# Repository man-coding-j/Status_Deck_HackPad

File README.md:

# Status_Deck_HackPad
Status_Deck is a fully custom-designed macro pad developed using the Seeed XIAO RP2040 microcontroller. The device incorporates a 2×3 diode-isolated key matrix, dual rotary encoders, and an I²C OLED display to provide real-time user feedback. The buttons are programmable to your needs, and this project was made for easy day-to-day use.

# Status_Deck

#Bill of Materials (BOM)

#| Item | Quantity | Description |

#| Seeed XIAO RP2040 | 1 | Microcontroller |

#| MX-style switches | 6 | Mechanical key switches |

#| 1N4148 Diodes | 6 | Matrix isolation |

#| Rotary Encoder | 2 | With push-button functionality |

#| 0.96" I²C OLED | 1 | SSD1306 display |

#| Keycaps | 6 | Compatible with MX switches |

#| Custom PCB | 1 | Designed in KiCad |

#| 3D Printed Case | 1 | Custom enclosure |

#| Screws / Standoffs | As needed | PCB mounting hardware |

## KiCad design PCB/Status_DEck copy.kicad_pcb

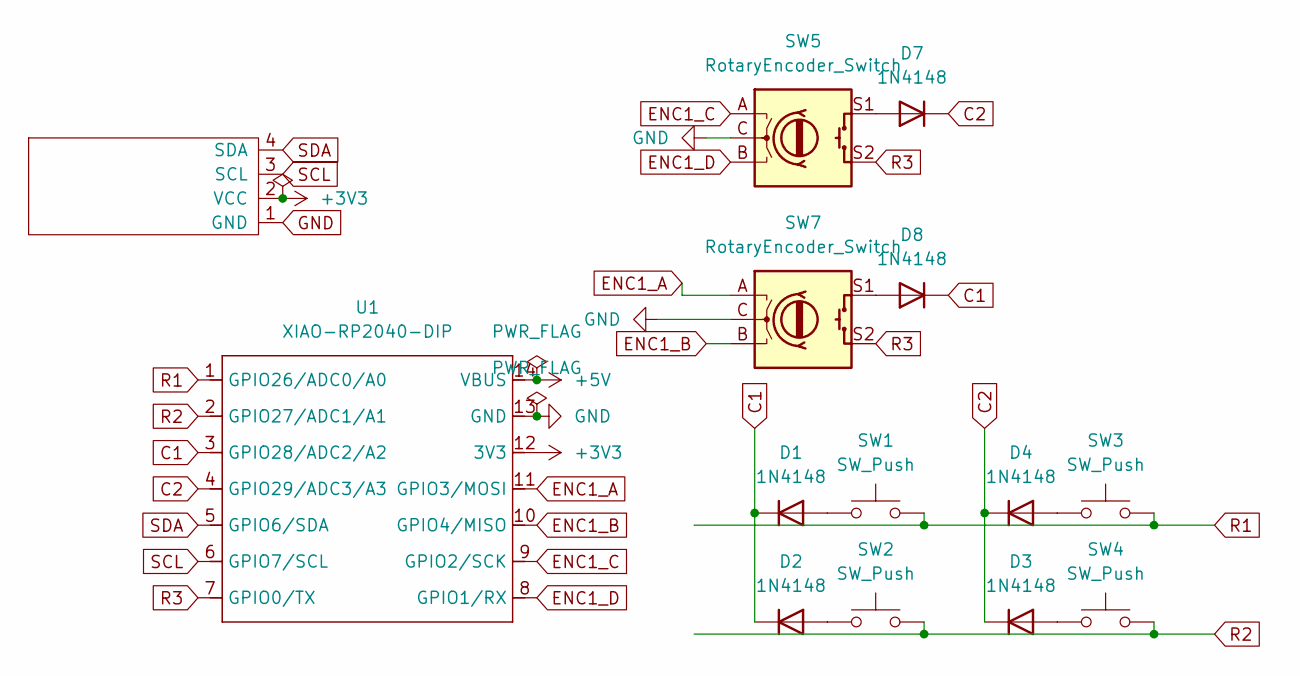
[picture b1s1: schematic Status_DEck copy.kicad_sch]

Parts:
D1, D2, D3, D4, D7, D8: 1N4148; D_DO-35_SOD27_P7.62mm_Horizontal
SW1, SW2, SW3, SW4: SW_Push; SW_Cherry_MX_1.00u_PCB
SW5, SW7: RotaryEncoder_Switch; RotaryEncoder_Alps_EC11E-Switch_Vertical_H20mm
U1: XIAO-RP2040-DIP
U3: SSD1306; SSD1306-0.91-OLED-4pin-128x32

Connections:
+3V3: U1.12 (3V3), U3.2 (VCC)
+5V: U1.14 (VBUS)
C1: D1.1 (K), D2.1 (K), D8.1 (K), U1.3 (GPIO28/ADC2/A2)
C2: D3.1 (K), D4.1 (K), D7.1 (K), U1.4 (GPIO29/ADC3/A3)
ENC1_A: SW7.A, U1.11 (GPIO3/MOSI)
ENC1_B: SW7.B, U1.10 (GPIO4/MISO)
ENC1_C: SW5.A, U1.9 (GPIO2/SCK)
ENC1_D: SW5.B, U1.8 (GPIO1/RX)
GND: SW5.C, SW7.C, U1.13 (GND), U3.1 (GND)
unnamed: D1.2 (A), SW1.1
unnamed: D2.2 (A), SW2.1
unnamed: D3.2 (A), SW4.1
unnamed: D4.2 (A), SW3.1
unnamed: D7.2 (A), SW5.S1
unnamed: D8.2 (A), SW7.S1
R1: SW1.2, SW3.2, U1.1 (GPIO26/ADC0/A0)
R2: SW2.2, SW4.2, U1.2 (GPIO27/ADC1/A1)
R3: SW5.S2, SW7.S2, U1.7 (GPIO0/TX)
SCL: U1.6 (GPIO7/SCL), U3.3 (SCL)
SDA: U1.5 (GPIO6/SDA), U3.4 (SDA)

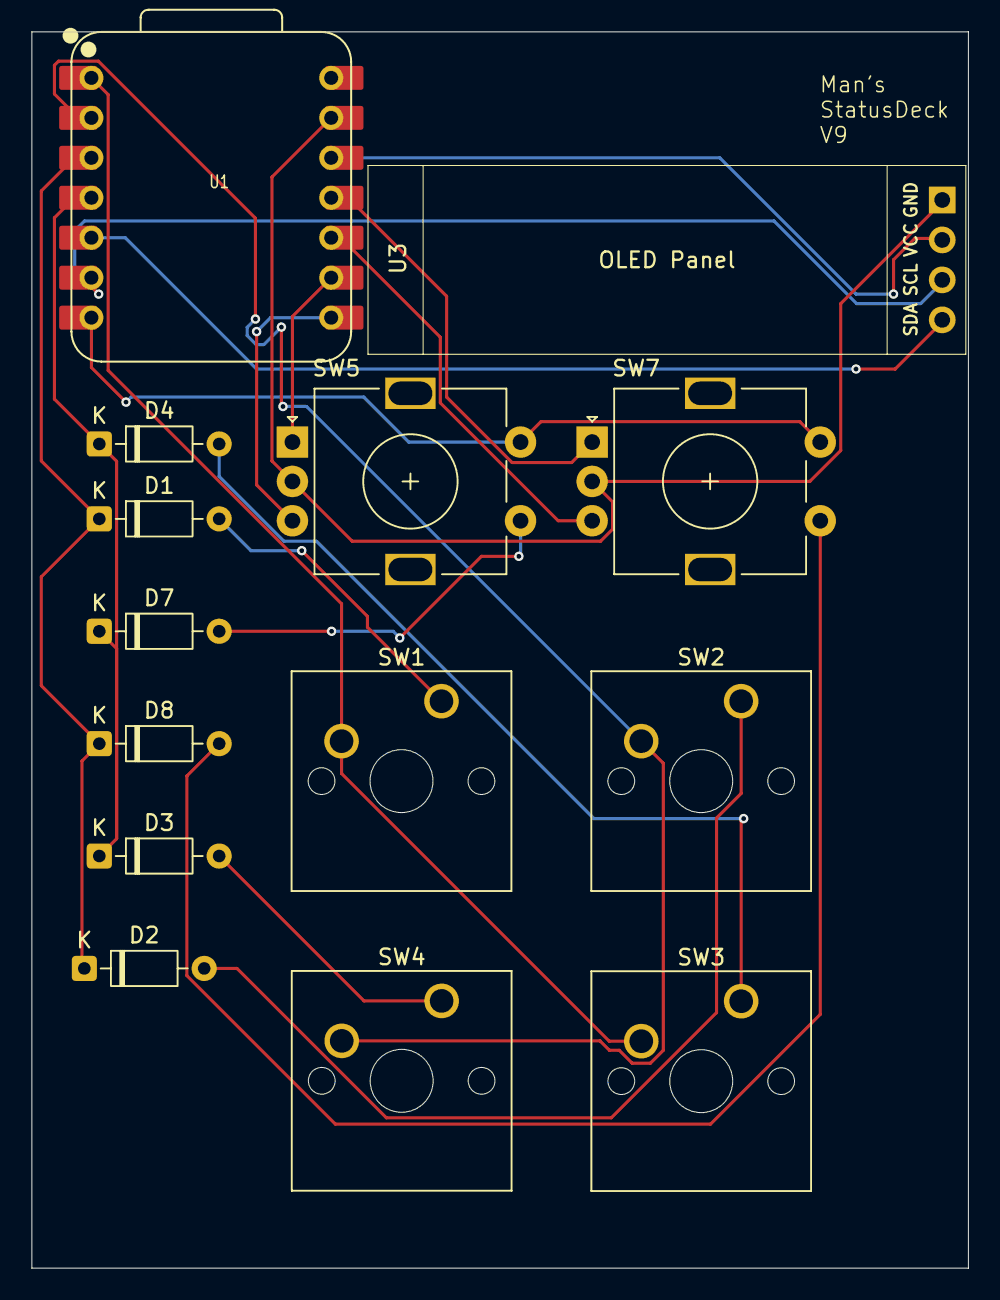
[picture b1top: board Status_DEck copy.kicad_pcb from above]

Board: 2 copper layers, 59.5 x 78.6 mm, 14 parts (0 on the bottom side), 19 nets.

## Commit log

2026-02-15 CAD
    This is the case of the hackpad. The PCB will sit inside and there is no top to show the interal parts of the PCB.
2026-02-15 PCB
    This is the PCB
2026-02-15 PCB
    This is the schematics and PCB i used for the Status_Deck
2026-02-15 CAD
    This is the 3D Case I used.
2026-02-15 filler
2026-02-15 Update Read.Me
    Updated project description to provide detailed information about the Status_Deck macro pad.
2026-02-15 Update README with images and project details
    Added images and improved project description.
